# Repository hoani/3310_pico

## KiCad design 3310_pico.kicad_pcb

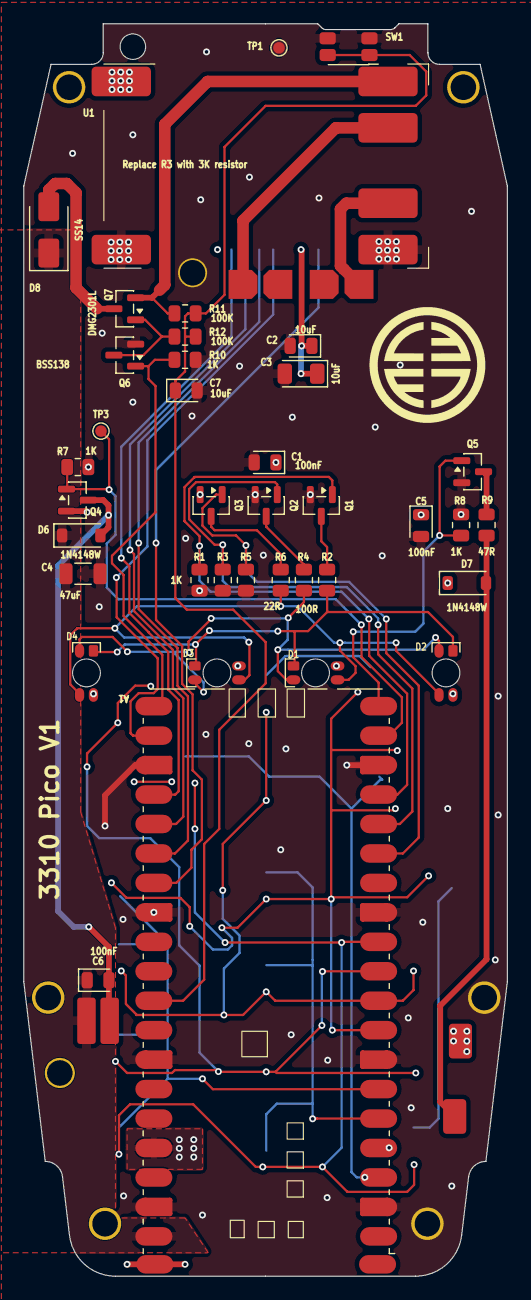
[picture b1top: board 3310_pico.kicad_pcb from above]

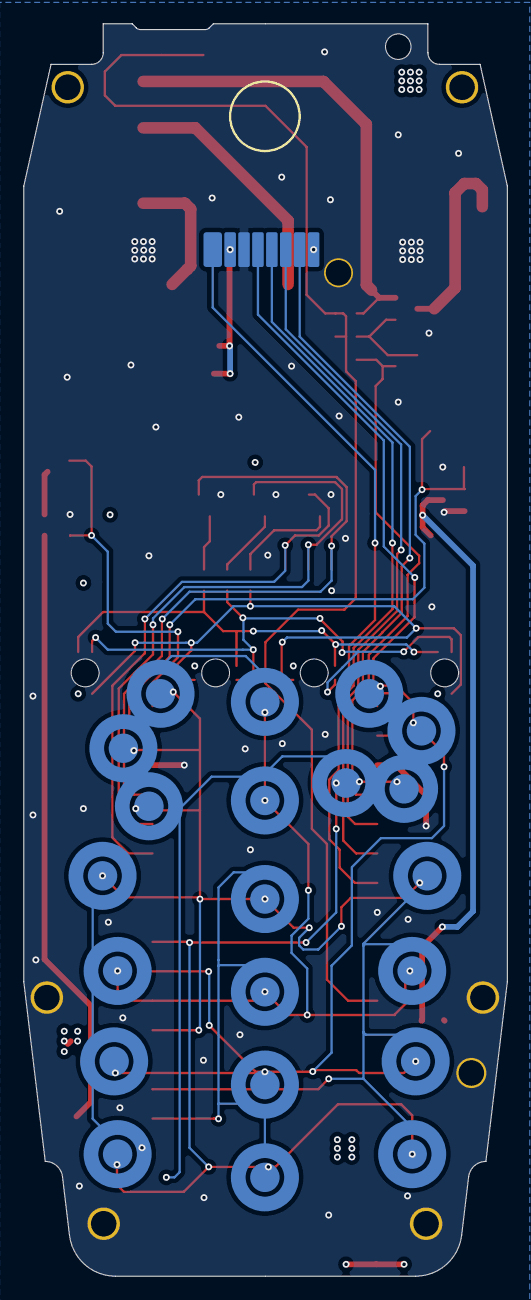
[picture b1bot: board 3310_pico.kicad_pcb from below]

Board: 4 copper layers, 41.7 x 108.0 mm, 43 parts (2 on the bottom side), 39 nets.

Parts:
A1: RaspberryPi_Pico; RaspberryPi_Pico_SMD_NoTP
B1: NokiaBuzzer
C1, C5, C6: 100nF; D_0805_2012Metric
C2, C7: 10uF; D_0805_2012Metric
C3: 10uF; D_1206_3216Metric
C4: 47uF; C_1206_3216Metric
D1, D2, D3, D4: VoidRGB
D6, D7: 1N4148W; D_SOD-123
D8: SS14; D_SMA
J1: PCDConn
J4: NokiaKeypad
J6: BatteryConn
M1: NokiaVibe
Q1, Q2, Q3, Q4, Q5, Q6: BSS138; SOT-23
Q7: DMG2301L; SOT-23
R1, R3, R5, R7, R8, R10: 1K; R_0805_2012Metric
R2: 82R; R_0805_2012Metric
R4: 100R; R_0805_2012Metric
R6: 22R; R_0805_2012Metric
R9: 47R; R_0805_2012Metric
R11, R12: 100K; R_0805_2012Metric
SW1: EVQP7A; SW_SPST_EVQP7A
TP1, TP3: TestPoint; TestPoint_Pad_D1.0mm
U1: TP4056_charger

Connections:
+3.3V: A1.36 (3V3), B1.1 (+), C1.1, C5.1, D1.2 (A), D2.2 (A), D3.2 (A), D4.2 (A), D7.1 (K), J1.8 (VCC)
+BATT: J6.1 (VP), U1.4 (Batt+)
-BATT: J6.4 (VN), U1.5 (Batt-)
/BacklightB: A1.15 (GPIO11), Q3.1 (G), R5.1
/BacklightG: A1.16 (GPIO12), Q2.1 (G), R3.1
/BacklightR: A1.17 (GPIO13), Q1.1 (G), R1.1
/Buzzer: A1.20 (GPIO15), Q5.1 (G), R8.1
/BuzzerOut: B1.2 (-), D7.2 (A), R9.1
/Col1: A1.5 (GPIO3), J4.5 (Col1)
/Col2: A1.6 (GPIO4), J4.6 (Col2)
/Col3: A1.7 (GPIO5), J4.7 (Col3)
/Col4: A1.4 (GPIO2), J4.8 (Col4)
/PcdCE: A1.22 (GPIO17), J1.4 (CE)
/PcdCLK: A1.24 (GPIO18), J1.7 (CLK)
/PcdDC: A1.26 (GPIO20), J1.5 (DC)
/PcdDin: A1.25 (GPIO19), J1.6 (DIN)
/PcdRst: A1.27 (GPIO21), J1.1 (nRST)
/PowerLatch: A1.21 (GPIO16), Q6.1 (G), R10.1
/Row1: A1.9 (GPIO6), J4.1 (Row1)
/Row2: A1.10 (GPIO7), J4.2 (Row2)
/Row3: A1.11 (GPIO8), J4.3 (Row3)
/Row4: A1.12 (GPIO9), J4.4 (Row4)
/VBattMeas: A1.31 (GPIO26_ADC0), C7.1, R11.2, R12.1, SW1.1 (A)
/Vibe: A1.19 (GPIO14), Q4.1 (G), R7.2, TP3.1 (1_1)
GND: A1.3 (GND), A1.8 (GND), A1.13 (GND), A1.18 (GND), A1.23 (GND), A1.28 (GND), A1.33 (AGND), A1.38 (GND), C1.2, C2.2, C3.2, C4.2, C5.2, C7.2, J1.3 (GND), Q1.2 (S), Q2.2 (S), Q3.2 (S), Q4.2 (S), Q5.2 (S), Q6.2 (S), R1.2, R3.2, R5.2, R7.1, R8.2, R10.2, SW1.2 (B), TP1.1 (1_1), U1.2 (V-), U1.6 (O-)
unnamed: D1.3 (BK), D2.3 (BK), D3.3 (BK), D4.3 (BK), R6.1
unnamed: D1.4 (GK), D2.4 (GK), D3.4 (GK), D4.4 (GK), R4.1
unnamed: D1.1 (RK), D2.1 (RK), D3.1 (RK), D4.1 (RK), R2.1
unnamed: C6.2, D6.2 (A), M1.2 (-), Q4.3 (D)
unnamed: D8.2 (A), Q7.3 (D)
unnamed: C2.1, C3.1, J1.2 (Vout)
unnamed: Q1.3 (D), R2.2
unnamed: Q2.3 (D), R4.2
unnamed: Q3.3 (D), R6.2
unnamed: Q5.3 (D), R9.2
unnamed: Q6.3 (D), Q7.1 (G), R12.2
unnamed: Q7.2 (S), R11.1, U1.3 (O+)
VBUS: A1.40 (VBUS), U1.1 (V+)
Vdrive: A1.39 (VSYS), C4.1, C6.1, D6.1 (K), D8.1 (K), M1.1 (+)
